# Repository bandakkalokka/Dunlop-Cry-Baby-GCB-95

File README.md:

# Dunlop-Cry-Baby-GCB-95
Design files for a customized Dunlop Cry Baby GCB-95

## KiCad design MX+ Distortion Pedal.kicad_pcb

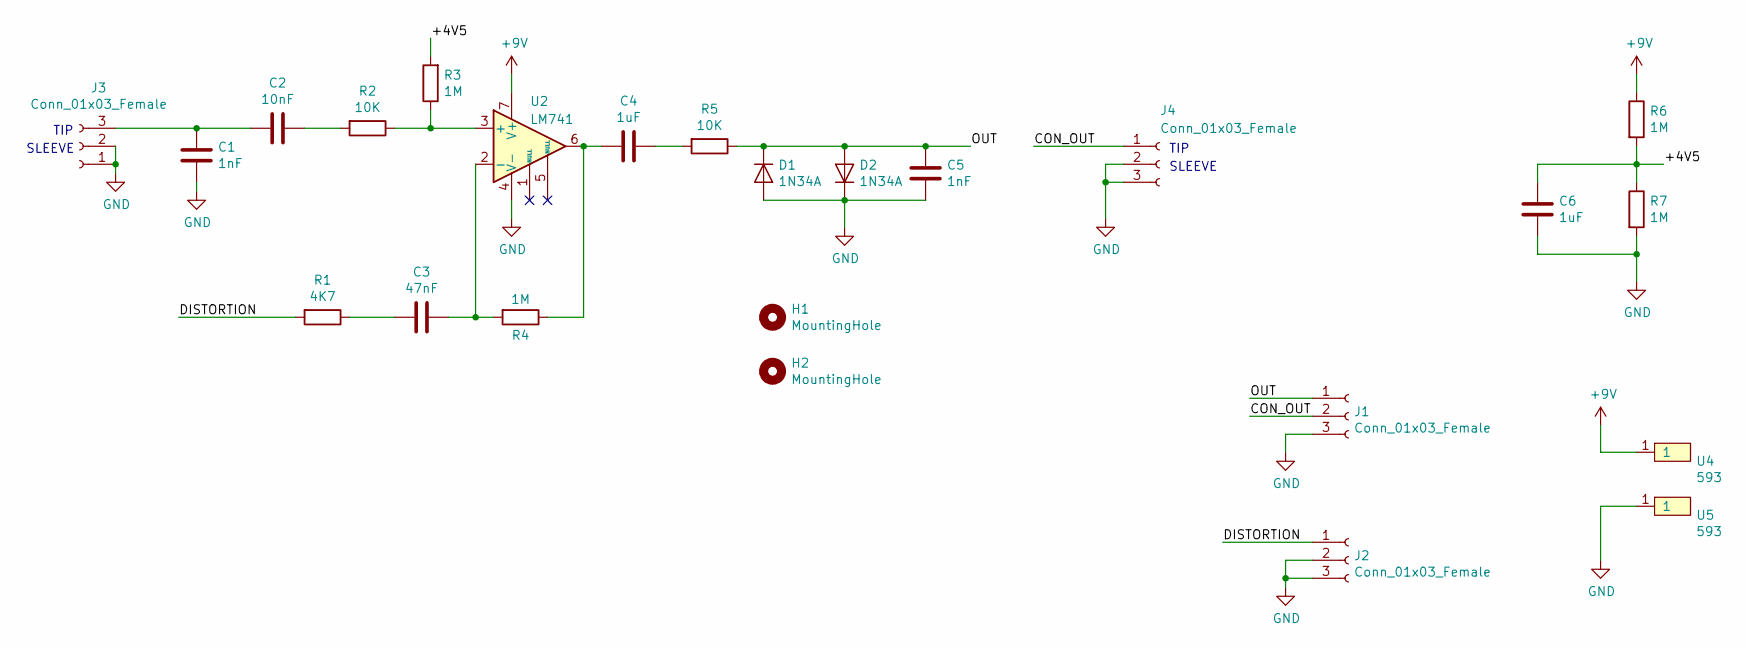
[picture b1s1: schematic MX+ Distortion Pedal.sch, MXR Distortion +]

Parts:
C1, C5: 1nF; C_0603_1608Metric_Pad1.05x0.95mm_HandSolder
C2: 10nF; C_0603_1608Metric_Pad1.05x0.95mm_HandSolder
C3: 47nF; C_0603_1608Metric_Pad1.05x0.95mm_HandSolder
C4, C6: 1uF; C_0603_1608Metric_Pad1.05x0.95mm_HandSolder
D1, D2: 1N34A; D_A-405_P12.70mm_Horizontal
H1, H2: MountingHole; MountingHole_5mm_Pad
J1, J2, J3, J4: Conn_01x03_Female; FanPinHeader_1x03_P2.54mm_Vertical
R1: 4K7; R_0603_1608Metric_Pad1.05x0.95mm_HandSolder
R2, R5: 10K; R_0603_1608Metric_Pad1.05x0.95mm_HandSolder
R3, R4, R6, R7: 1M; R_0603_1608Metric_Pad1.05x0.95mm_HandSolder
U2: LM741; DIP-8_W7.62mm_LongPads
U4, U5: 593

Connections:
+9V: R6.1, U2.7 (V+), U4.1
/+4V5: C6.1, R3.2, R6.2, R7.1
/CON_OUT: J1.2, J4.1
/DISTORTION: J2.1, R1.2
/OUT: C5.1, D1.1 (K), D2.2 (A), J1.1, R5.1
GND: C1.2, C5.2, C6.2, D1.2 (A), D2.1 (K), J1.3, J2.2, J2.3, J3.1, J3.2, J4.2, J4.3, R7.2, U2.4 (V-), U5.1
unnamed: C1.1, C2.2, J3.3
unnamed: C2.1, R2.2
unnamed: C3.1, R4.2, U2.2 (-)
unnamed: C3.2, R1.1
unnamed: C4.1, R5.2
unnamed: C4.2, R4.1, U2.6
unnamed: R2.1, R3.1, U2.3 (+)

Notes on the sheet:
TIP
SLEEVE

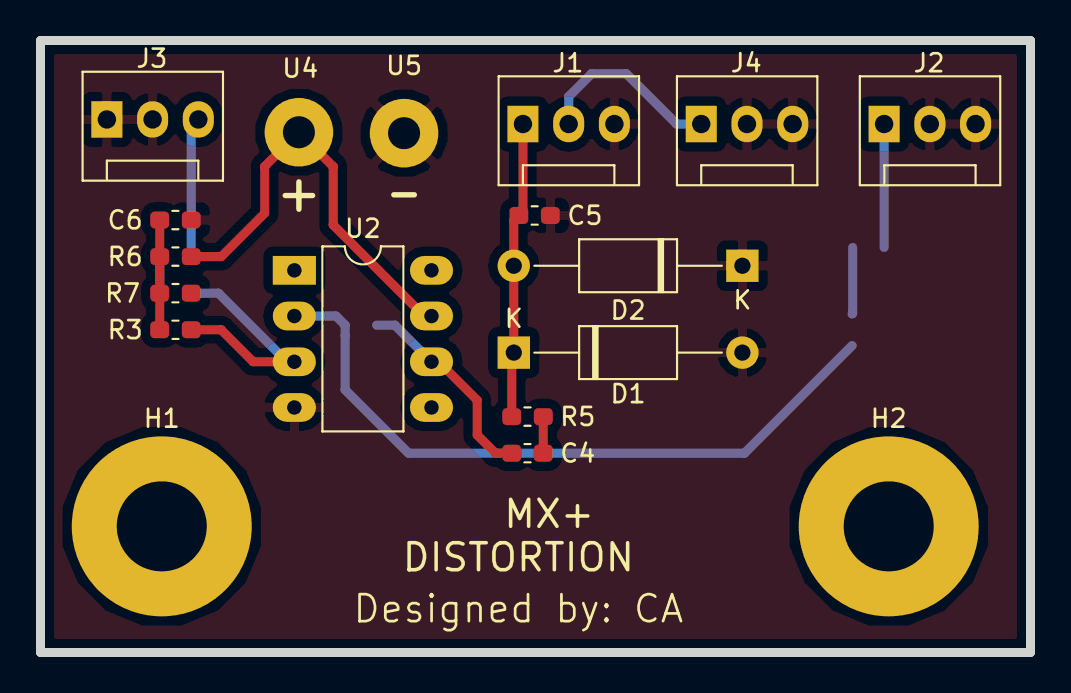
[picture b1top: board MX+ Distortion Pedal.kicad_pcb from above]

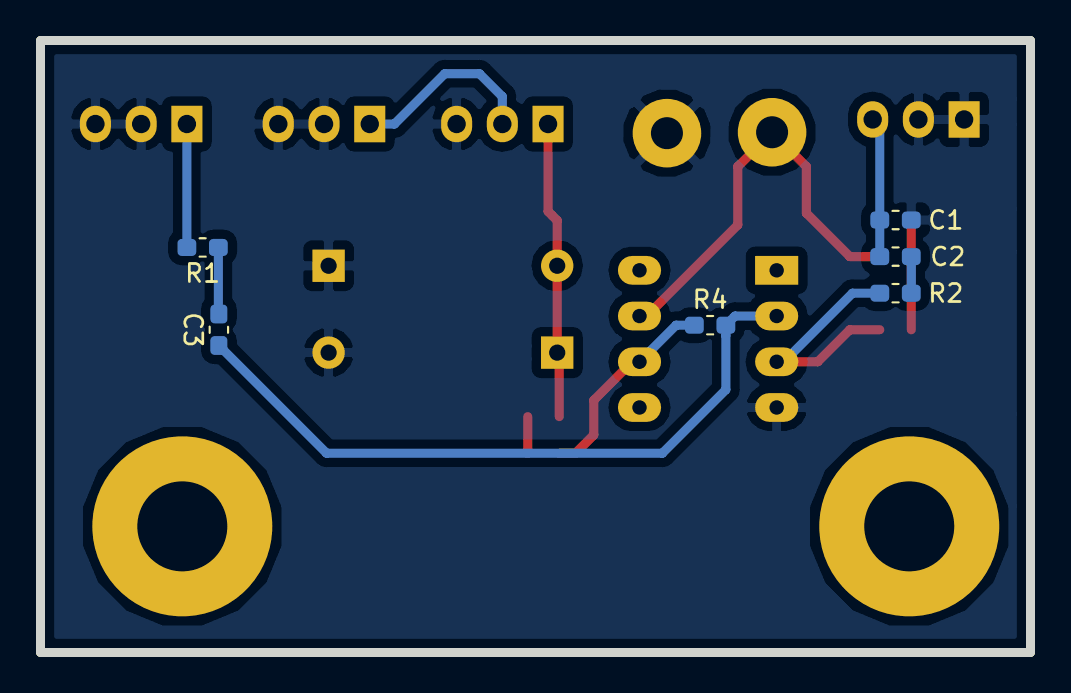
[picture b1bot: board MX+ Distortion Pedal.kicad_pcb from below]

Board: 2 copper layers, 55.0 x 34.0 mm, 24 parts (6 on the bottom side), 13 nets.

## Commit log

2018-12-30 Add .gitignore
2018-12-31 Add *.zip to gitignore
2018-12-31 Made few connections
2020-05-30 Port from Altium to KiCAD
